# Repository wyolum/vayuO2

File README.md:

# vayuO2
controller board for oxygen concentrator

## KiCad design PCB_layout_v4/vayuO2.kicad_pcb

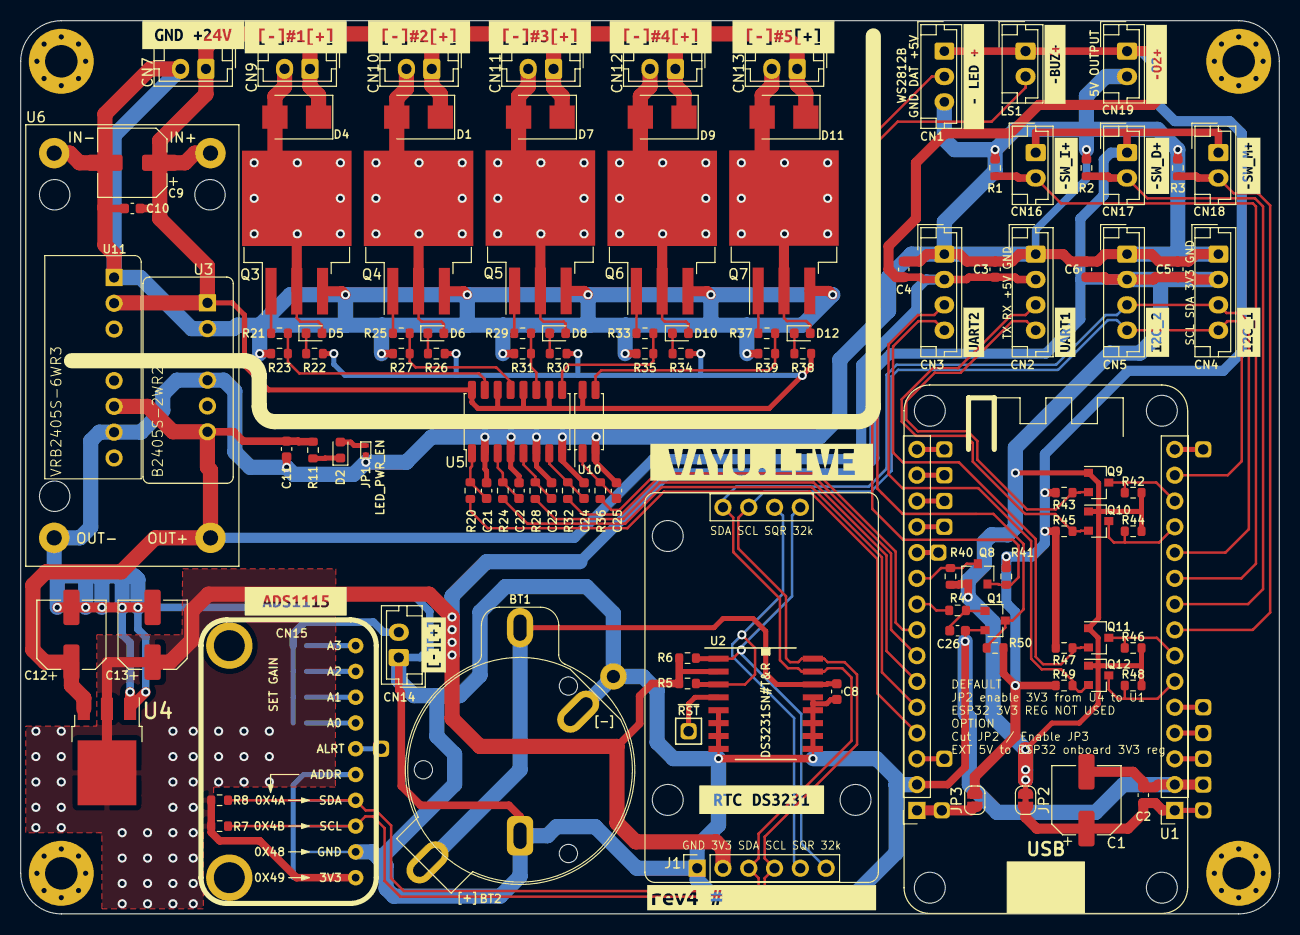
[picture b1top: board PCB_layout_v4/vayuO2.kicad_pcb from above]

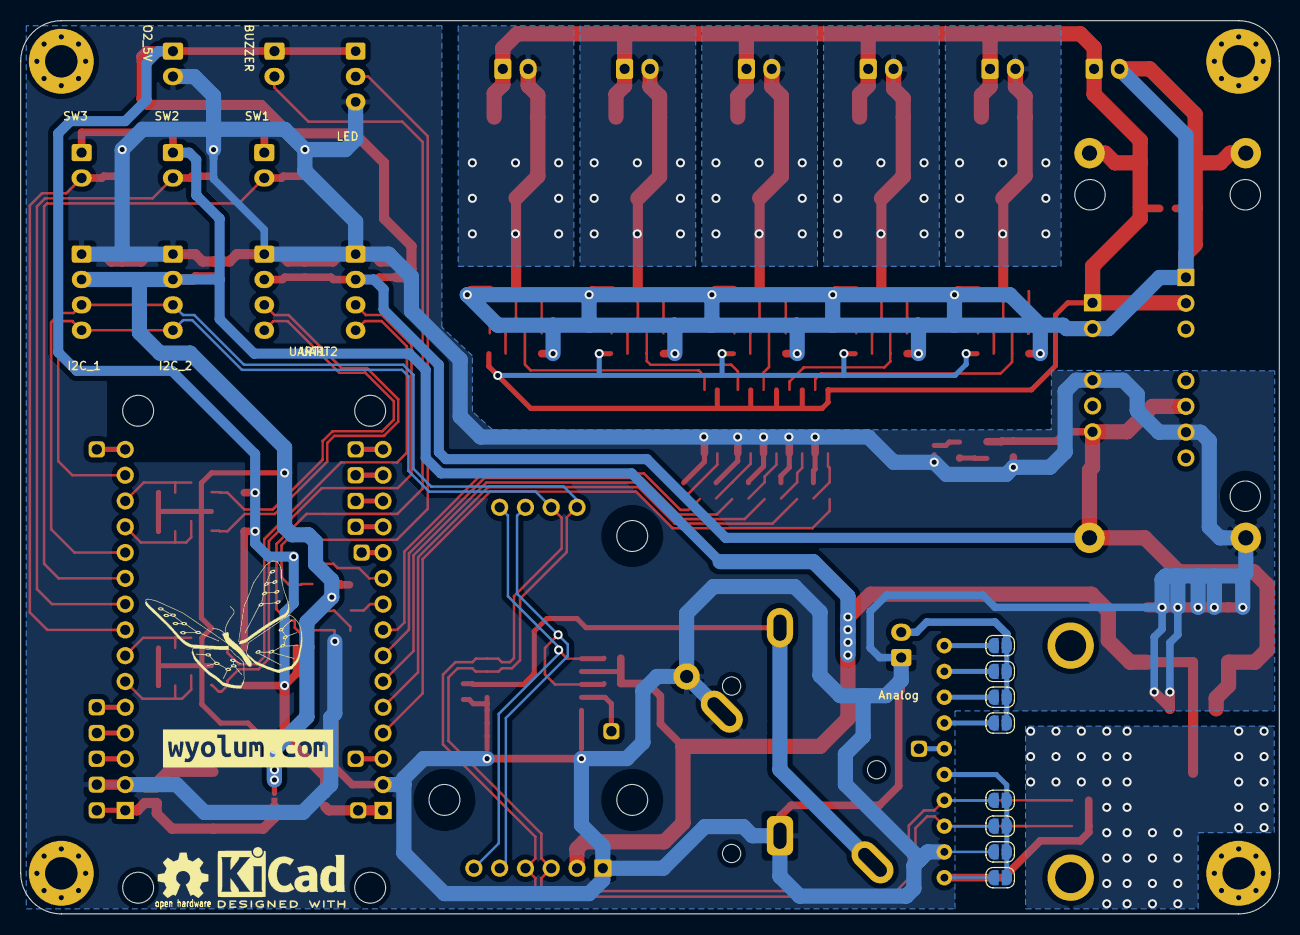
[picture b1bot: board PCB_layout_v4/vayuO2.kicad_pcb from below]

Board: 2 copper layers, 124.0 x 88.0 mm, 164 parts (12 on the bottom side), 78 nets.

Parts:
BT1: Batt_RTC; cr2032_02
BT2: Batt_RTC; cr2032_03
C1: 100uF/6V3; CP_Elec_6.3x5.3
C2: 1uF/10V; C_0603_1608Metric
C3, C4, C5, C6, C8, C10, C11, C21, C22, C23, C24, C25, C26: 100nF; C_0603_1608Metric
C9, C12: 10uF/25V; CP_Elec_6.3x7.7
C13: 22uF/25V; CP_Elec_6.3x7.7
CN1: Conn_LED; JST_EH_B3B-EH-A_1x03_P2.50mm_Vertical
CN2: UART1; JST_EH_B4B-EH-A_1x04_P2.50mm_Vertical
CN3: UART2; JST_EH_B4B-EH-A_1x04_P2.50mm_Vertical
CN4: I2C_1; JST_EH_B4B-EH-A_1x04_P2.50mm_Vertical
CN5: I2C_2; JST_EH_B4B-EH-A_1x04_P2.50mm_Vertical
CN7: 24VDC; JST_EH_B2B-EH-A_1x02_P2.50mm_Vertical
CN9, CN10, CN11, CN12, CN13: OUT; JST_EH_B2B-EH-A_1x02_P2.50mm_Vertical
CN14: Conn_Analog; JST_EH_B2B-EH-A_1x02_P2.50mm_Vertical
CN15: Conn_ADS1115; ADS1115
CN16: Conn_S1; JST_EH_B2B-EH-A_1x02_P2.50mm_Vertical
CN17: Conn_S2; JST_EH_B2B-EH-A_1x02_P2.50mm_Vertical
CN18: Conn_S3; JST_EH_B2B-EH-A_1x02_P2.50mm_Vertical
CN19: Conn_O2_5V; JST_EH_B2B-EH-A_1x02_P2.50mm_Vertical
D1, D4, D7, D9, D11: B220A-13-F; D_SMB
D2: LED_PWR; LED_0603_1608Metric
D5, D6, D8, D10, D12: LED; LED_0603_1608Metric
G1: LOGO_WL; logo_butterfly_silk_15x12
G2: KiCad; KiCad-Logo2_6mm_SilkScreen
G3: OSHW; Logo_silk_OSHW_6x6mm
HB1, HB2, HB3, HB4: mtg_hole_3mm; MountingHole_3.2mm_M3_Pad_Via
J1: DS3231_BO; DS3231_breakout
J2, J3, J4, J5, J6, J7, J8, J9, J10, J11, J12, J13, J14, J15: Conn_01x01; BreakOutPad2
JP1: LED_PWR_EN; R_0402
JP2: Jumper_3V_EN; SolderJumper-2_P1.3mm_Bridged_RoundedPad1.0x1.5mm
JP3: Jumper_5V_EN; SolderJumper-2_P1.3mm_Open_RoundedPad1.0x1.5mm
LS1: Piezo; JST_EH_B2B-EH-A_1x02_P2.50mm_Vertical
Q1: MMBT3904; SOT-23
Q3, Q4, Q5, Q6, Q7: IRF540NS; TO-263-3_TabPin2
Q8, Q9, Q10, Q11, Q12: BSS138; SOT-23
R1, R2, R3, R5, R6, R40, R41, R42, R43, R44, R45, R46, R47, R48, R49: 10k; R_0603_1608Metric
R4: 220E; R_0603_1608Metric
R7, R8: 4K7; R_0603_1608Metric
R11, R23, R27, R31, R35, R39, R50: 1k; R_0603_1608Metric
R20, R24, R28, R32, R36: 330E; R_0603_1608Metric
R21, R25, R29, R33, R37: 100E; R_0603_1608Metric
R22, R26, R30, R34, R38: 3k3; R_0603_1608Metric
R51, R52, R53, R54, R55, R56, R57, R58: 0E; SolderJumper-2_P1.3mm_Open_RoundedPad1.0x1.5mm
TP2: ~RST; BreakOutPad
U1: ESP32_breakout; ESP32_DOIT_V2_Module
U2: DS3231SN#T&R; DS3231
U3: B2405S-2WR2; DC_DC_conv_2W
U4: LM1117-33; TO-252-3_TabPin2
U5: PS2801-4; SO-16_5.3x10.2mm_P1.27mm
U6: 24V_BUCK; DC_DC_buck_LM2596
U10: PS2801-1; SO-4_5.3x2.7mm_P1.27mm
U11: DC_DC_buck_6W; DC_DC_conv_6W
kibuzzard-61A5CB8A: G***; label_RTC
kibuzzard-61A5D4B0, kibuzzard-61A53326: G***; label
kibuzzard-615EFBF6: G***; label_wyolum
kibuzzard-615EFE7C: #G***; label
kibuzzard-615EFE42: #G***; label_24V
kibuzzard-615EFF0D: #G***; label_out2
kibuzzard-615EFF1D: #G***; label_out4
kibuzzard-615EFF16: #G***; label_out3
kibuzzard-615EFF24: #G***; label_out5
kibuzzard-615F0BBC: #G***; label_vayu
kibuzzard-615F01C3: #G***; label_ads1115
kibuzzard-615F02BE: #G***; label_I2C_1
kibuzzard-615F03BD: #G***; label_uart1
kibuzzard-615F04CC: #G***; label_O2
kibuzzard-615F08E2: #G***; label_sw_i
kibuzzard-615F0246: #G***; label_pm
kibuzzard-615F0326: #G***; label_I2C_2
kibuzzard-615F0408: #G***; label_uart2
kibuzzard-615F0547: #G***; label_LED
kibuzzard-615F0858: #G***; label_sw_m
kibuzzard-615F0877: #G***; label_sw_d

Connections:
+24V: C9.1, C10.1, CN7.1, CN9.1, CN10.1, CN11.1, CN12.1, CN13.1, D1.1, D4.1, D7.1, D9.1, D11.1, R22.2, R26.2, R30.2, R34.2, R38.2, U3.VIN, U5.10, U5.12, U5.14, U5.16, U6.VIN, U10.4, U11.VIN
/3V3: C5.2, C6.2, C13.1, CN4.2, CN5.2, CN15.1, CN16.1, CN17.1, CN18.1, J1.2, JP2.1, Q8.1, Q9.1, Q10.1, Q11.1, Q12.1, R5.1, R6.1, R7.1, R8.1, R40.1, R42.1, R44.1, R46.1, R48.1, R51.1, U2.2, U4.2
/5V: C3.2, C4.2, C11.1, C12.1, CN1.1, CN2.2, CN3.2, CN19.1, JP3.2, LS1.1, R11.2, R41.1, R43.1, R45.1, R47.1, R49.1, R50.1, U3.VO, U4.3, U6.VO, U11.VO
/A0: CN15.7, R55.1
/A1: CN15.8, R56.1
/A2: CN15.9, R57.1
/A3: CN15.10, R58.1
/ADDR: CN15.5, R51.2, R52.2, R53.2, R54.2
/ALRT: CN15.6, J7.1
/DAT: CN1.2, Q8.2, R41.2
/EN: J15.1, U1.16
/IO2: J8.1, U1.4
/IO4: J9.1, U1.5
/IO13: J6.1, U1.28
/IO15: J5.1, U1.3
/IO23: J14.1, U1.15
/LED_RGB: Q8.3, R40.2, U1.21
/OUT1: R20.1, U1.27
/OUT2: R24.1, U1.26
/OUT3: R28.1, U1.25
/OUT4: R32.1, U1.24
/OUT5: R36.1, U1.23
/RX0: CN2.3, Q10.2, R45.2
/RX2: CN3.3, Q12.2, R49.2
/RXD0: Q10.3, R44.2, U1.12
/RXD2: Q12.3, R48.2, U1.6
/SCL: CN4.4, CN5.4, CN15.3, J1.4, R7.2, R53.1, U1.14, U2.16
/SDA: CN4.3, CN5.3, CN15.4, J1.3, R8.2, R54.1, U1.11, U2.15
/SENSOR_VN: J12.1, U1.18
/SENSOR_VP: J13.1, U1.17
/SPKR: R4.2, U1.22
/SW_D: CN17.2, R2.1, U1.9
/SW_I: CN16.2, R1.1, U1.10
/SW_M: CN18.2, R3.1, U1.8
/TX0: CN2.4, Q9.2, R43.2
/TX2: CN3.4, Q11.2, R47.2
/TXD0: Q9.3, R42.2, U1.13
/TXD2: Q11.3, R46.2, U1.7
/mosfets/OP1: CN9.2, D4.2, D5.2, Q3.2
/mosfets/OP2: CN10.2, D1.2, D6.2, Q4.2
/mosfets/OP3: CN11.2, D7.2, D8.2, Q5.2
/mosfets/OP4: CN12.2, D9.2, D10.2, Q6.2
/mosfets/OP5: CN13.2, D11.2, D12.2, Q7.2
/mosfets/filter1: C21.1, R20.2, U5.1
/mosfets/filter2: C22.1, R24.2, U5.3
/mosfets/filter3: C23.1, R28.2, U5.5
/mosfets/filter4: C24.1, R32.2, U5.7
/mosfets/filter5: C25.1, R36.2, U10.1
/rtc_ds3231/32kHz: J1.6, R6.2, U2.1
/rtc_ds3231/BAT: BT1.1, BT2.1, C8.1, U2.14
/rtc_ds3231/RESET: TP2.1, U2.4
/rtc_ds3231/SQR: J1.5, R5.2, U2.3
GND: BT1.2, BT2.2, C1.2, C2.2, C3.1, C4.1, C5.1, C6.1, C8.2, C11.2, C12.2, C13.2, C21.2, C22.2, C23.2, C24.2, C25.2, C26.1, CN1.3, CN2.1, CN3.1, CN4.1, CN5.1, CN14.1, CN15.2, CN19.2, J1.1, J4.1, JP1.1, Q1.2, R1.2, R2.2, R3.2, R52.1, U1.2, U1.29, U2.5, U2.6, U2.7, U2.8, U2.9, U2.10, U2.11, U2.12, U2.13, U3.GND, U4.1, U5.2, U5.4, U5.6, U5.8, U6.GND, U10.2, U11.GND
GNDPWR: C9.2, C10.2, CN7.2, Q3.3, Q4.3, Q5.3, Q6.3, Q7.3, R23.1, R27.1, R31.1, R35.1, R39.1, U3.GNDPWR, U6.GNDPWR, U11.GNDPWR
unnamed: C1.1, C2.1, J2.1, JP2.2, U1.1
unnamed: C26.2, Q1.1, R4.1
unnamed: CN14.2, R55.2, R56.2, R57.2, R58.2
unnamed: D2.1, R11.1
unnamed: D2.2, JP1.2
unnamed: D5.1, R22.1
unnamed: D6.1, R26.1
unnamed: D8.1, R30.1
unnamed: D10.1, R34.1
unnamed: D12.1, R38.1
unnamed: J3.1, JP3.1, U1.30
unnamed: J10.1, U1.20
unnamed: J11.1, U1.19
unnamed: LS1.2, Q1.3, R50.2
unnamed: Q3.1, R21.1
unnamed: Q4.1, R25.1
unnamed: Q5.1, R29.1
unnamed: Q6.1, R33.1
unnamed: Q7.1, R37.1
unnamed: R21.2, R23.2, U5.15
unnamed: R25.2, R27.2, U5.13
unnamed: R29.2, R31.2, U5.11
unnamed: R33.2, R35.2, U5.9
unnamed: R37.2, R39.2, U10.3

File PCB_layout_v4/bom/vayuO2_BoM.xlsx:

Id | Designator | Package | Quantity | Designation
1 | C1 | CP_Elec_6.3x5.3 | 1 | 100uF/6V3
2 | C2 | C_0603_1608Metric | 1 | 1uF/10V
3 | C12,C9 | CP_Elec_6.3x7.7 | 2 | 10uF/25V
4 | C13 | CP_Elec_6.3x7.7 | 1 | 22uF/25V
5 | C25,C26,C24,C23,C22,C21,C11,C10,C8,C6,C5,C4,C3 | C_0603_1608Metric | 13 | 100nF
6 | D2 | LED_0603_1608Metric | 1 | LED_PWR
7 | D6,D12,D10,D8,D5 | LED_0603_1608Metric | 5 | LED
8 | D11,D9,D7,D4,D1 | D_SMB | 5 | B220A-13-F
9 | Q1 | SOT-23 | 1 | MMBT3904
10 | Q7,Q6,Q5,Q4,Q3 | TO-263-3_TabPin2 | 5 | IRF540NS
11 | Q11,Q12,Q10,Q9,Q8 | SOT-23 | 5 | BSS138
12 | R3,R49,R48,R47,R46,R45,R44,R43,R42,R41,R40,R6,R5,R2,R1 | R_0603_1608Metric | 15 | 10k
13 | R4 | R_0603_1608Metric | 1 | 220E
14 | R8,R7 | R_0603_1608Metric | 2 | 4K7
15 | R25,R37,R33,R29,R21 | R_0603_1608Metric | 5 | 100E
16 | R26,R30,R38,R34,R22 | R_0603_1608Metric | 5 | 3k3
17 | R27,R11,R50,R39,R35,R31,R23 | R_0603_1608Metric | 7 | 1k
18 | R36,R32,R28,R24,R20 | R_0603_1608Metric | 5 | 330E
19 | U2 | DS3231 | 1 | DS3231SN#T&R
20 | U4 | TO-252-3_TabPin2 | 1 | LM1117-33
21 | U5 | SO-16_5.3x10.2mm_P1.27mm | 1 | PS2801-4
22 | U10 | SO-4_5.3x2.7mm_P1.27mm | 1 | PS2801-1
23 | BT1 | cr2032_02 | 1 | Batt_RTC
24 | BT2 | cr2032_03 | 1 | Batt_RTC
25 | CN1 | JST_EH_B3B-EH-A_1x03_P2.50mm_Vertical | 1 | Conn_LED
26 | CN2 | JST_EH_B4B-EH-A_1x04_P2.50mm_Vertical | 1 | UART1
27 | CN3 | JST_EH_B4B-EH-A_1x04_P2.50mm_Vertical | 1 | UART2
28 | CN4 | JST_EH_B4B-EH-A_1x04_P2.50mm_Vertical | 1 | I2C_1
29 | CN5 | JST_EH_B4B-EH-A_1x04_P2.50mm_Vertical | 1 | I2C_2
30 | CN7 | JST_EH_B2B-EH-A_1x02_P2.50mm_Vertical | 1 | 24VDC
31 | CN9,CN13,CN12,CN11,CN10 | JST_EH_B2B-EH-A_1x02_P2.50mm_Vertical | 5 | OUT
32 | CN14 | JST_EH_B2B-EH-A_1x02_P2.50mm_Vertical | 1 | Conn_Analog
33 | CN15 | ADS1115 | 1 | Conn_ADS1115
34 | CN16 | JST_EH_B2B-EH-A_1x02_P2.50mm_Vertical | 1 | Conn_S1
35 | CN17 | JST_EH_B2B-EH-A_1x02_P2.50mm_Vertical | 1 | Conn_S2
36 | CN18 | JST_EH_B2B-EH-A_1x02_P2.50mm_Vertical | 1 | Conn_S3
37 | CN19 | JST_EH_B2B-EH-A_1x02_P2.50mm_Vertical | 1 | Conn_O2_5V
38 | J1 | DS3231_breakout | 1 | DS3231_BO
39 | LS1 | JST_EH_B2B-EH-A_1x02_P2.50mm_Vertical | 1 | Piezo
40 | U1 | ESP32_DOIT_V2_Module | 1 | ESP32_breakout
41 | U3 | DC_DC_conv_2W | 1 | B2405S-2WR2
42 | U6 | DC_DC_buck_LM2596 | 1 | 24V_BUCK
43 | U11 | DC_DC_conv_6W | 1 | DC_DC_buck_6W

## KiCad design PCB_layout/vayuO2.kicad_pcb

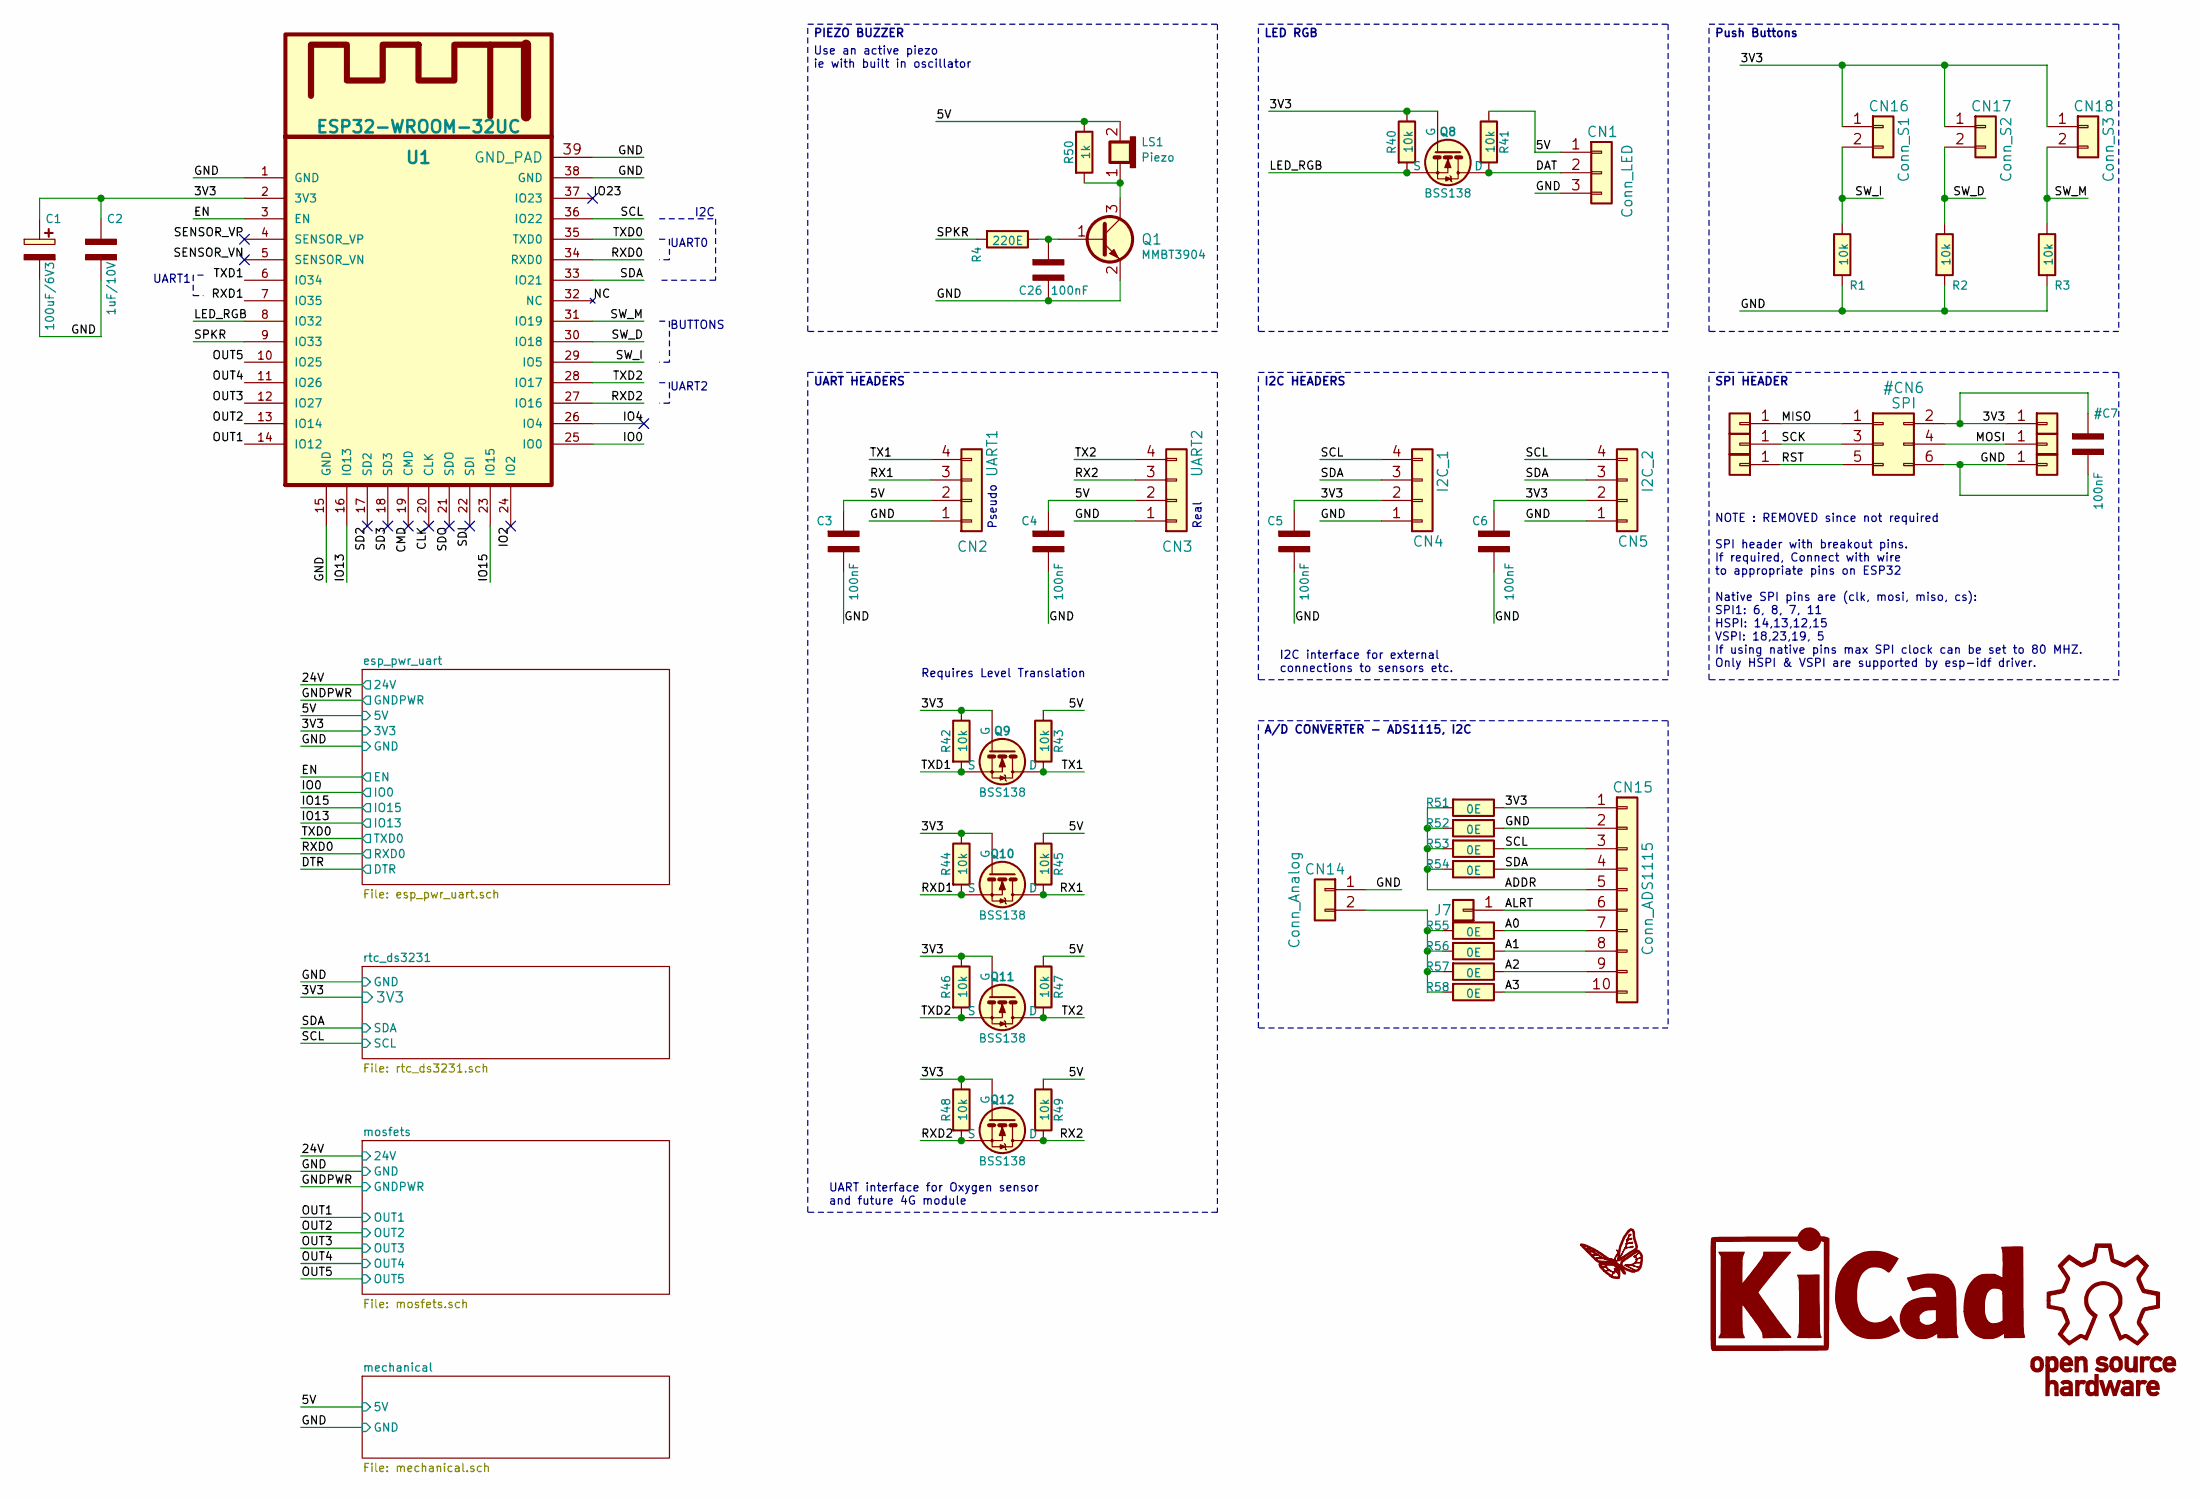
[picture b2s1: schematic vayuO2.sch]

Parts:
C1: 100uF/6V3; CP_Elec_8x10
C2: 1uF/10V; C_0603_1608Metric
C3, C4, C5, C6, C26: 100nF; C_0603_1608Metric
CN1: Conn_LED; JST_EH_B3B-EH-A_1x03_P2.50mm_Vertical
CN2: UART1; JST_EH_B4B-EH-A_1x04_P2.50mm_Vertical
CN3: UART2; JST_EH_B4B-EH-A_1x04_P2.50mm_Vertical
CN4: I2C_1; JST_EH_B4B-EH-A_1x04_P2.50mm_Vertical
CN5: I2C_2; JST_EH_B4B-EH-A_1x04_P2.50mm_Vertical
CN14: Conn_Analog; JST_EH_B2B-EH-A_1x02_P2.50mm_Vertical
CN15: Conn_ADS1115; ADS1115
CN16: Conn_S1; JST_EH_B2B-EH-A_1x02_P2.50mm_Vertical
CN17: Conn_S2; JST_EH_B2B-EH-A_1x02_P2.50mm_Vertical
CN18: Conn_S3; JST_EH_B2B-EH-A_1x02_P2.50mm_Vertical
G1: LOGO_WL; logo_butterfly_silk_15x12
G2: KiCad; KiCad-Logo2_6mm_SilkScreen
G3: OSHW; Logo_silk_OSHW_6x6mm
J7: Conn_01x01; BreakOutPad
LS1: Piezo; JST_EH_B2B-EH-A_1x02_P2.50mm_Vertical
Q1: MMBT3904; SOT-23
Q8, Q9, Q10, Q11, Q12: BSS138; SOT-23
R1, R2, R3, R40, R41, R42, R43, R44, R45, R46, R47, R48, R49: 10k; R_0603_1608Metric
R4: 220E; R_0603_1608Metric
R50: 1k; R_0603_1608Metric
R51, R52, R53, R54, R55, R56, R57, R58: 0E; SolderJumper-2_P1.3mm_Open_RoundedPad1.0x1.5mm
U1: ESP32-WROOM-32UC; ESP_wroom_32_ext_ant

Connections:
/5V: C3.2 (-), C4.2 (-), CN1.1, CN2.2, CN3.2, LS1.2 (+), R41.1, R43.1, R45.1, R47.1, R49.1, R50.1; also elsewhere on the board
/A0: CN15.7, R55.1
/A1: CN15.8, R56.1
/A2: CN15.9, R57.1
/A3: CN15.10, R58.1
/ADDR: CN15.5, R51.2, R52.2, R53.2, R54.2
/ALRT: CN15.6, J7.1
/CLK: U1.20 (CLK)
/CMD: U1.19 (CMD)
/DAT: CN1.2, Q8.2 (D), R41.2
/EN: U1.3 (EN); also elsewhere on the board
/IO0: U1.25 (IO0); also elsewhere on the board
/IO2: U1.24 (IO2)
/IO4: U1.26 (IO4)
/IO13: U1.16 (IO13); also elsewhere on the board
/IO15: U1.23 (IO15); also elsewhere on the board
/IO23: U1.37 (IO23)
/LED_RGB: Q8.3 (S), R40.2, U1.8 (IO32)
/NC: U1.32 (NC)
/OUT1: U1.14 (IO12); also elsewhere on the board
/OUT2: U1.13 (IO14); also elsewhere on the board
/OUT3: U1.12 (IO27); also elsewhere on the board
/OUT4: U1.11 (IO26); also elsewhere on the board
/OUT5: U1.10 (IO25); also elsewhere on the board
/RX1: CN2.3, Q10.2 (D), R45.2
/RX2: CN3.3, Q12.2 (D), R49.2
/RXD0: U1.34 (RXD0); also elsewhere on the board
/RXD1: Q10.3 (S), R44.2, U1.7 (IO35)
/RXD2: Q12.3 (S), R48.2, U1.27 (IO16)
/SCL: CN4.4, CN5.4, CN15.3, R53.1, U1.36 (IO22); also elsewhere on the board
/SD2: U1.17 (SD2)
/SD3: U1.18 (SD3)
/SDA: CN4.3, CN5.3, CN15.4, R54.1, U1.33 (IO21); also elsewhere on the board
/SDI: U1.22 (SDI)
/SDO: U1.21 (SDO)
/SENSOR_VN: U1.5 (SENSOR_VN)
/SENSOR_VP: U1.4 (SENSOR_VP)
/SPKR: R4.2, U1.9 (IO33)
/SW_D: CN17.2, R2.1, U1.30 (IO18)
/SW_I: CN16.2, R1.1, U1.29 (IO5)
/SW_M: CN18.2, R3.1, U1.31 (IO19)
/TX1: CN2.4, Q9.2 (D), R43.2
/TX2: CN3.4, Q11.2 (D), R47.2
/TXD0: U1.35 (TXD0); also elsewhere on the board
/TXD1: Q9.3 (S), R42.2, U1.6 (IO34)
/TXD2: Q11.3 (S), R46.2, U1.28 (IO17)
unnamed: C26.2 (-), Q1.1 (B), R4.1
unnamed: CN14.2, R55.2, R56.2, R57.2, R58.2
unnamed: LS1.1 (-), Q1.3 (C), R50.2

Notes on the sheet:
Push Buttons
BUTTONS
I2C
UART0
Native SPI pins are (clk, mosi, miso, cs): SPI1: 6, 8, 7, 11 HSPI: 14,13,12,15 VSPI: 18,23,19, 5 If using native pins max SPI clock can be set to 80 MHZ. Only HSPI & VSPI are supported by esp-idf driver.
NOTE : REMOVED since not required SPI header with breakout pins. If required, Connect with wire to appropriate pins on ESP32
I2C interface for external connections to sensors etc.
SPI HEADER
I2C HEADERS
UART2
UART interface for Oxygen sensor and future 4G module
UART HEADERS
Requires Level Translation
UART1
Pseudo
Real
LED RGB
PIEZO BUZZER
Use an active piezo ie with built in oscillator
A/D CONVERTER - ADS1115, I2C

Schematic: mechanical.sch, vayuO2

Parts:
CN19: Conn_O2_5V; JST_EH_B2B-EH-A_1x02_P2.50mm_Vertical
HB1, HB2, HB3, HB4: mtg_hole_3mm; MountingHole_3.2mm_M3_Pad_Via
MB1, MB2, MB3, MB4, MB5, MB6: Mouse_Bite; mouse-bite-2.54mm-slot_OSH
U7: Sensor_O2_US
U10: Sensor_O2_US_narrow

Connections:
/5V: CN19.1; also elsewhere on the board

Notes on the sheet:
MECHANICAL FOOTPRINT FOR ULTRASONIC O2 SENSOR
MOUSE BITES
5V Supply for O2 Sensor
ALTERNATE MECHANICAL FOOTPRINT FOR ULTRASONIC O2 SENSOR

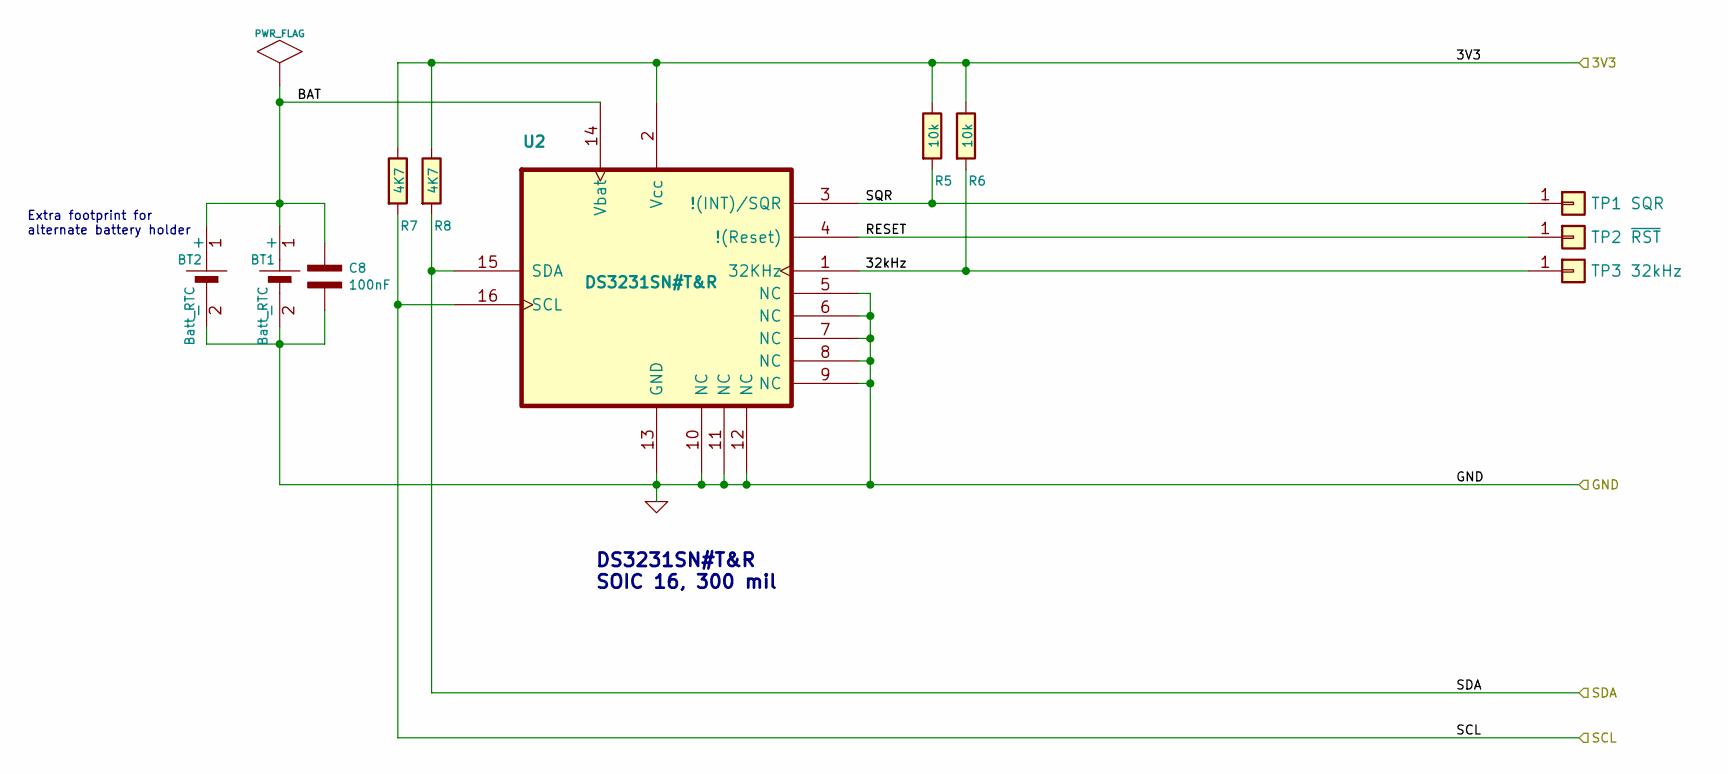
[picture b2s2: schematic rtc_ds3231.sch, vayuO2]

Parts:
BT1: Batt_RTC; cr2032_02; Digikey BU2032SM-HD-GCT-ND
BT2: Batt_RTC; cr2032_03; Digikey BU2032SM-HD-GCT-ND
C8: 100nF; C_0603_1608Metric
R5, R6: 10k; R_0603_1608Metric
R7, R8: 4K7; R_0603_1608Metric
TP1: SQR; BreakOutPad
TP2: ~RST; BreakOutPad
TP3: 32kHz; BreakOutPad
U2: DS3231SN#T&R; DS3231

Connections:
/SCL: R7.2, U2.16 (SCL); also elsewhere on the board
/SDA: R8.2, U2.15 (SDA); also elsewhere on the board
/rtc_ds3231/32kHz: R6.2, TP3.1, U2.1 (32KHz)
/rtc_ds3231/BAT: BT1.1 (+), BT2.1 (+), C8.1 (+), U2.14 (Vbat)
/rtc_ds3231/RESET: TP2.1, U2.4 (!(Reset))
/rtc_ds3231/SQR: R5.2, TP1.1, U2.3 (!(INT)/SQR)

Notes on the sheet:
DS3231SN#T&R SOIC 16, 300 mil
Extra footprint for alternate battery holder

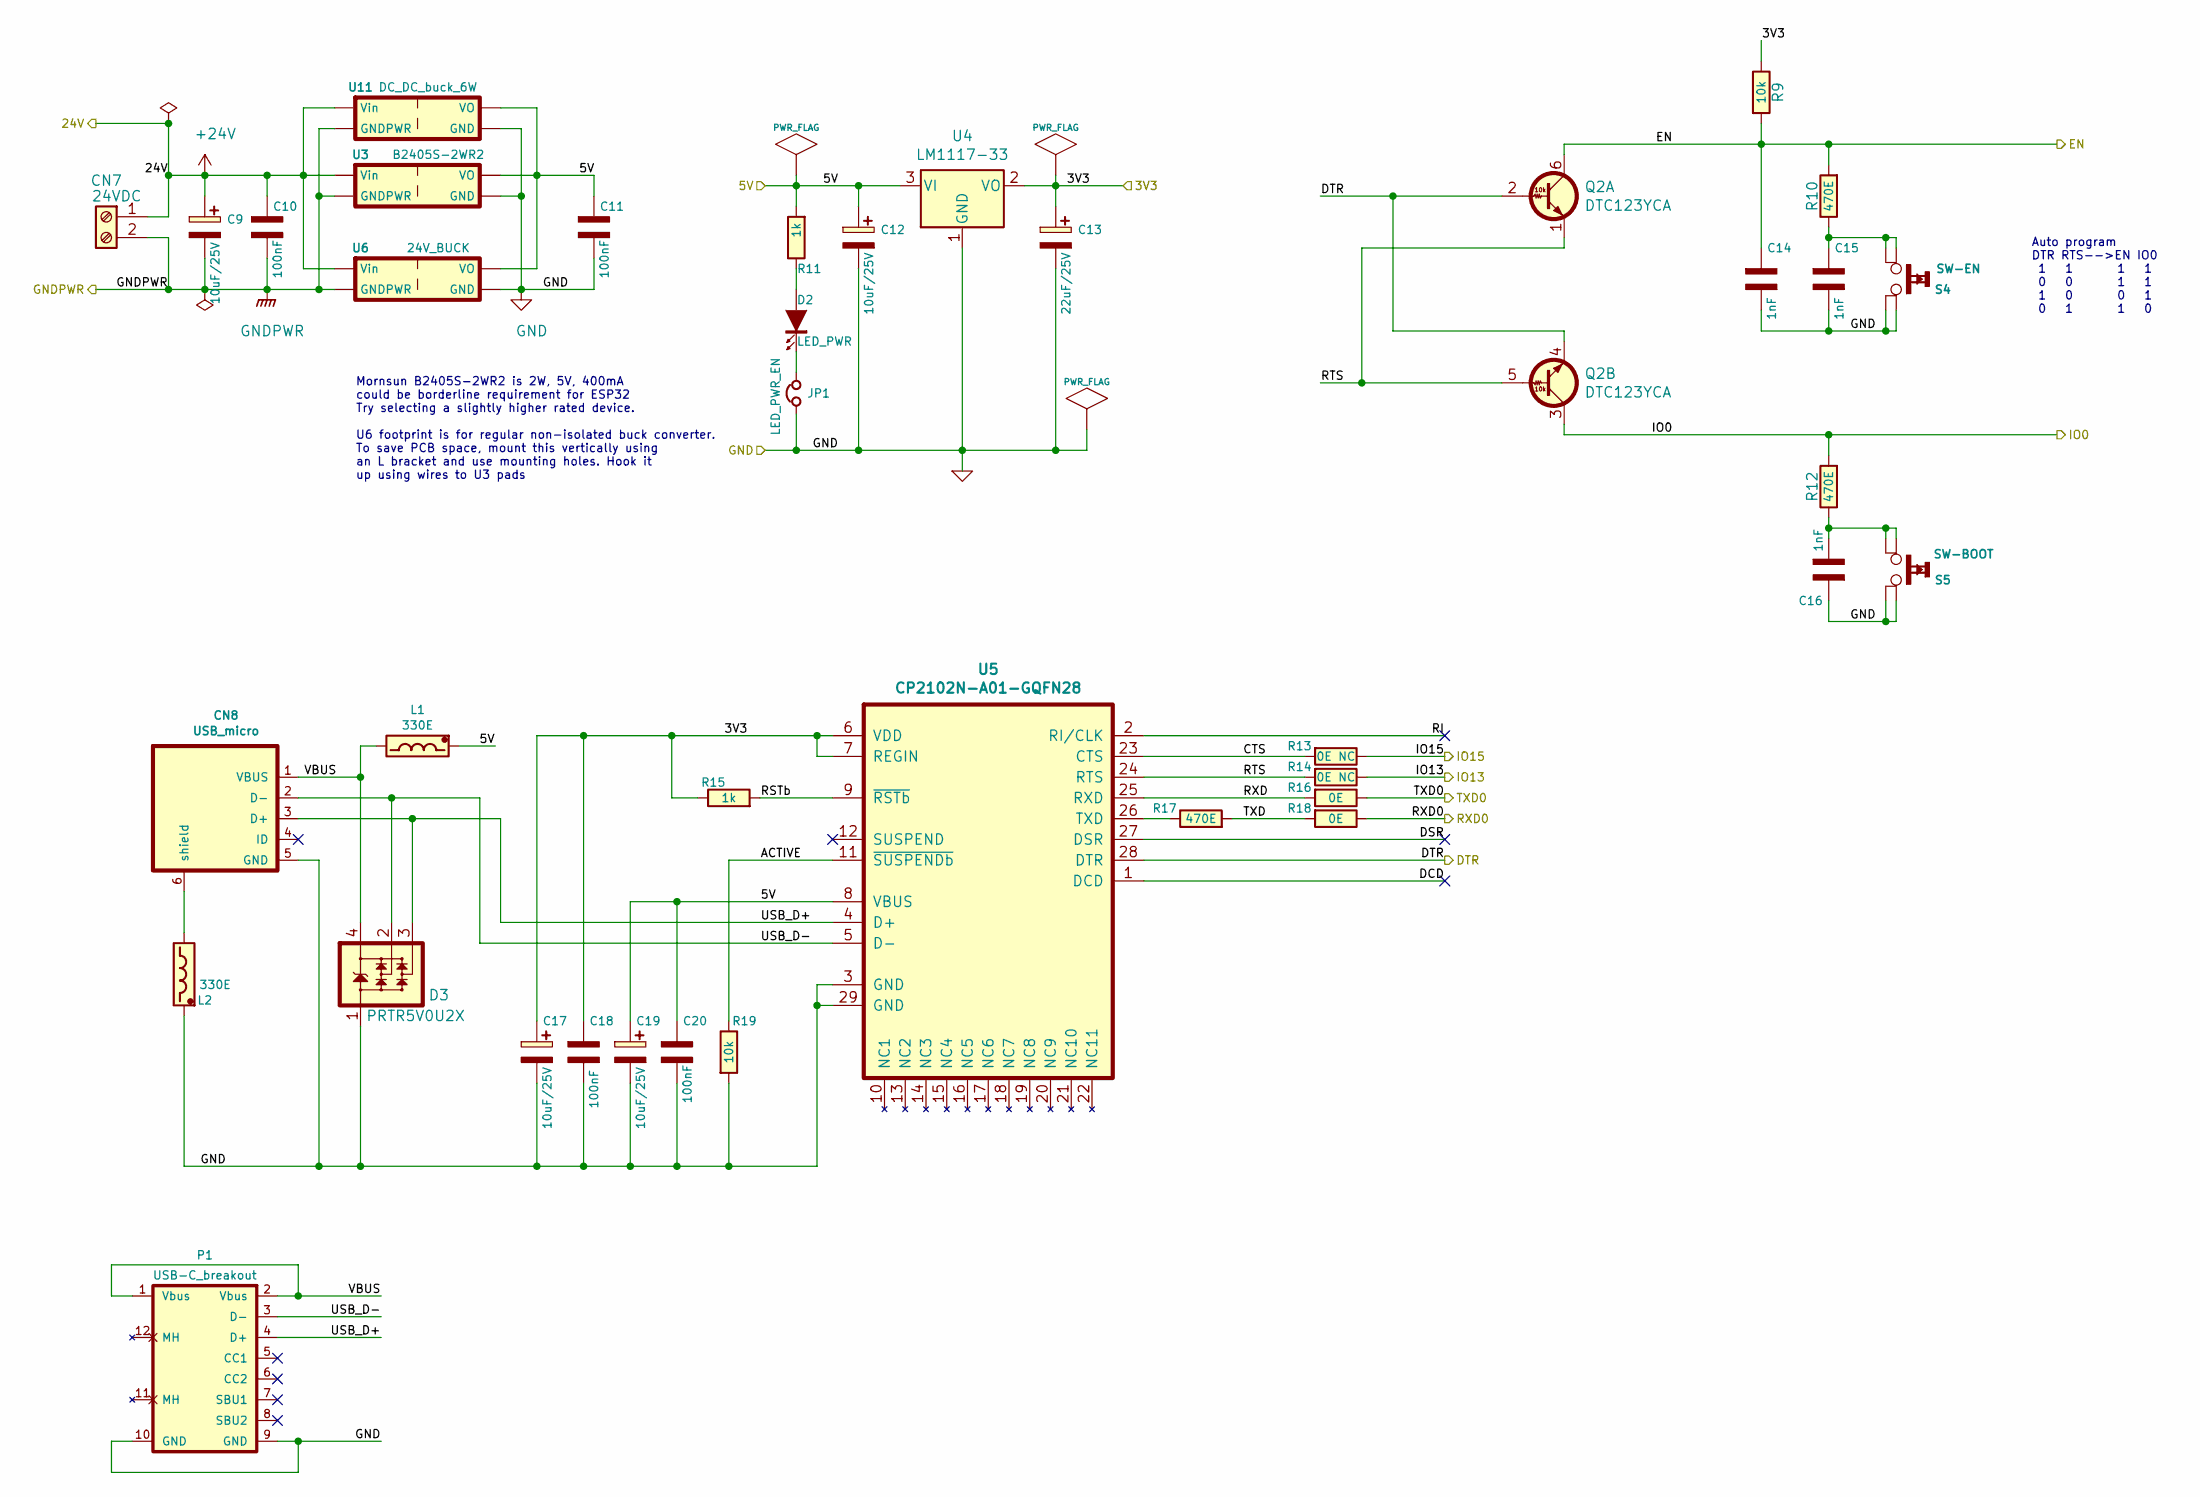
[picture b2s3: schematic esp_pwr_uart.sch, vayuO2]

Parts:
C9, C12, C17: 10uF/25V; CP_Elec_6.3x7.7
C10, C11, C18, C20: 100nF; C_0603_1608Metric
C13: 22uF/25V; CP_Elec_6.3x7.7
C14, C15, C16: 1nF; C_0603_1608Metric
C19: 10uF/25V; CP_Elec_6.3x5.4
CN7: 24VDC; TerminalBlock_Wurth_1377-2_Horizontal
CN8: USB_micro; USB_Micro-B_seeed-320010561
D2: LED_PWR; LED_0603_1608Metric
D3: PRTR5V0U2X; SOT-143
JP1: LED_PWR_EN; R_0402
L1, L2: 330E; R_0603_1608Metric
P1: USB-C_breakout; USB-C_bout
Q2: DTC123YCA; SOT-363_SC-70-6
R9, R19: 10k; R_0603_1608Metric
R10, R12, R17: 470E; R_0603_1608Metric
R11, R15: 1k; R_0603_1608Metric
R13, R14: 0E NC; R_0603_1608Metric
R16, R18: 0E; R_0603_1608Metric
S4: SW-EN; SW_SMD_311020004
S5: SW-BOOT; SW_SMD_311020004
U3: B2405S-2WR2; DC_DC_conv_2W
U4: LM1117-33; TO-252-3_TabPin2
U5: CP2102N-A01-GQFN28; QFN-28-1EP_5x5mm_Pitch0.5mm
U6: 24V_BUCK; DC_DC_buck_LM2596_Vertical
U11: DC_DC_buck_6W; DC_DC_conv_6W

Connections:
+24V: C9.1 (+), C10.1 (+), CN7.1, U3.VIN (Vin), U6.VIN (Vin), U11.VIN (Vin); also elsewhere on the board
/5V: C11.1 (+), C12.1 (+), C19.1 (+), C20.1 (+), L1.1, R11.2, U3.VO, U4.3 (VI), U5.8 (VBUS), U6.VO, U11.VO; also elsewhere on the board
/DTR: Q2.2 (B1), Q2.4 (E2), U5.28 (DTR)
/EN: C14.1 (+), Q2.6 (C1), R9.2, R10.2; also elsewhere on the board
/IO0: Q2.3 (C2), R12.2; also elsewhere on the board
/IO13: R14.1; also elsewhere on the board
/IO15: R13.1; also elsewhere on the board
/RXD0: R18.1; also elsewhere on the board
/TXD0: R16.1; also elsewhere on the board
/esp_pwr_uart/ACTIVE: R19.1, U5.11 (~SUSPENDb)
/esp_pwr_uart/CTS: R13.2, U5.23 (CTS)
/esp_pwr_uart/DCD: U5.1 (DCD)
/esp_pwr_uart/DSR: U5.27 (DSR)
/esp_pwr_uart/RI: U5.2 (RI/CLK)
/esp_pwr_uart/RSTb: R15.2, U5.9 (~RSTb)
/esp_pwr_uart/RTS: Q2.1 (E1), Q2.5 (B2), R14.2, U5.24 (RTS)
/esp_pwr_uart/RXD: R16.2, U5.25 (RXD)
/esp_pwr_uart/TXD: R17.2, R18.2
/esp_pwr_uart/USB_D+: CN8.3 (D+), D3.3, P1.4 (D+), U5.4 (D+)
/esp_pwr_uart/USB_D-: CN8.2 (D-), D3.2, P1.3 (D-), U5.5 (D-)
/esp_pwr_uart/VBUS: CN8.1 (VBUS), D3.4, L1.2, P1.1 (Vbus), P1.2 (Vbus)
GNDPWR: C9.2 (-), C10.2 (-), CN7.2, U3.GNDPWR, U6.GNDPWR, U11.GNDPWR; also elsewhere on the board
unnamed: C15.1 (+), R10.1, S4.2, S4.4
unnamed: C16.2 (-), R12.1, S5.2, S5.4
unnamed: CN8.6 (shield), L2.2
unnamed: D2.1 (A), R11.1
unnamed: D2.2 (K), JP1.2
unnamed: R17.1, U5.26 (TXD)

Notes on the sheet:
Auto program DTR RTS-->EN IO0 1 1 1 1 0 0 1 1 1 0 0 1 0 1 1 0
Mornsun B2405S-2WR2 is 2W, 5V, 400mA could be borderline requirement for ESP32 Try selecting a slightly higher rated device. U6 footprint is for regular non-isolated buck converter. To save PCB space, mount this vertically using an L bracket and use mounting holes. Hook it up using wires to U3 pads
